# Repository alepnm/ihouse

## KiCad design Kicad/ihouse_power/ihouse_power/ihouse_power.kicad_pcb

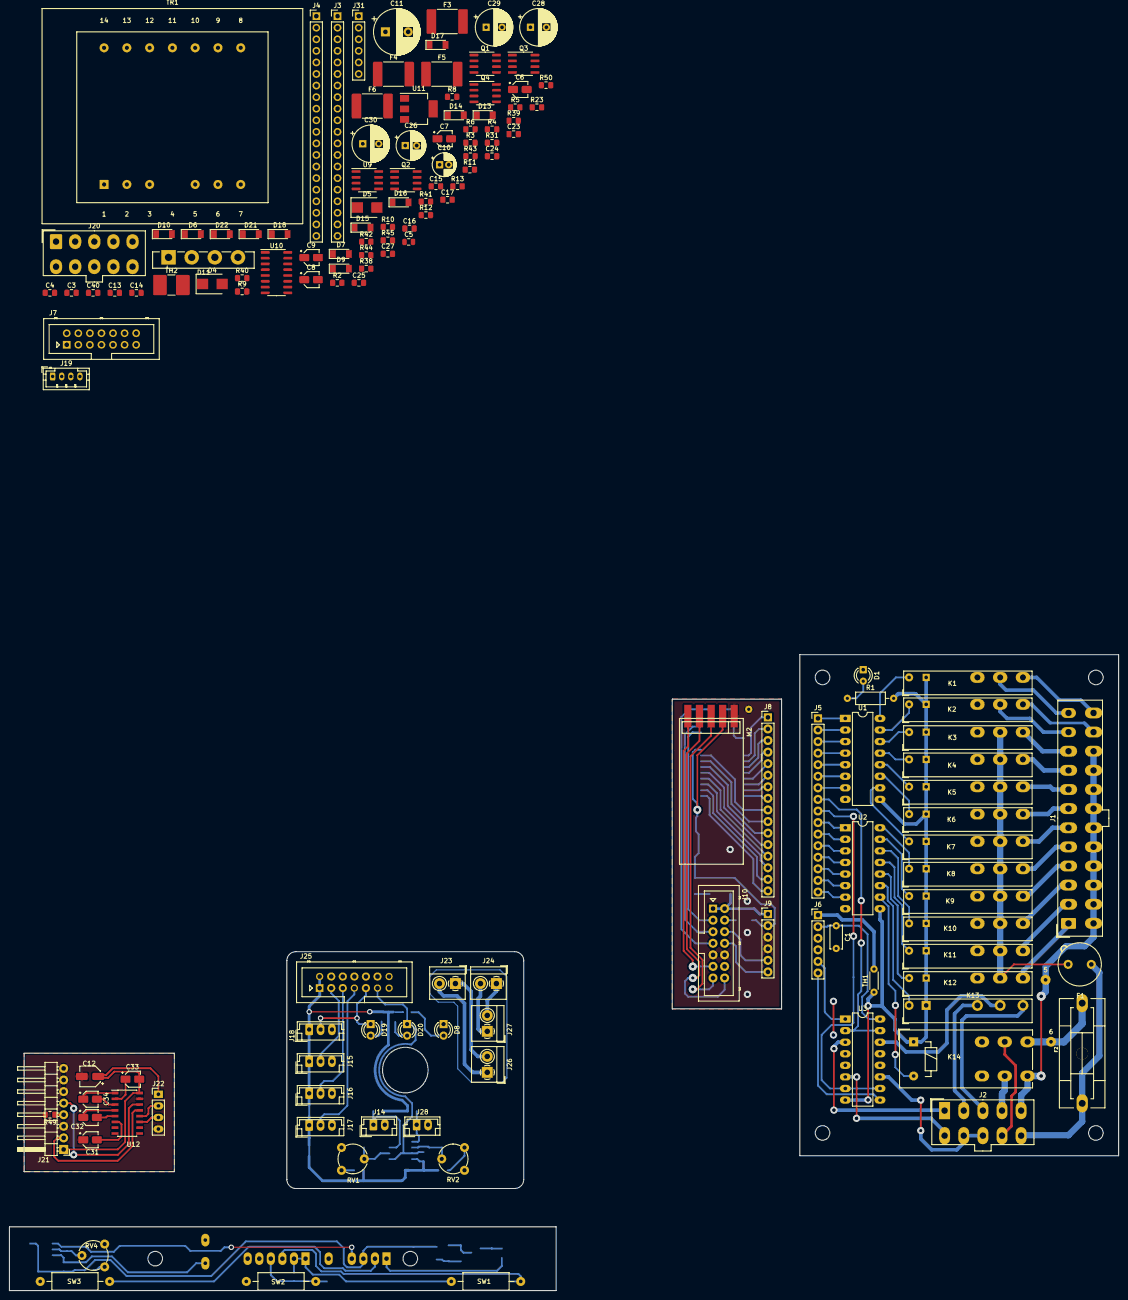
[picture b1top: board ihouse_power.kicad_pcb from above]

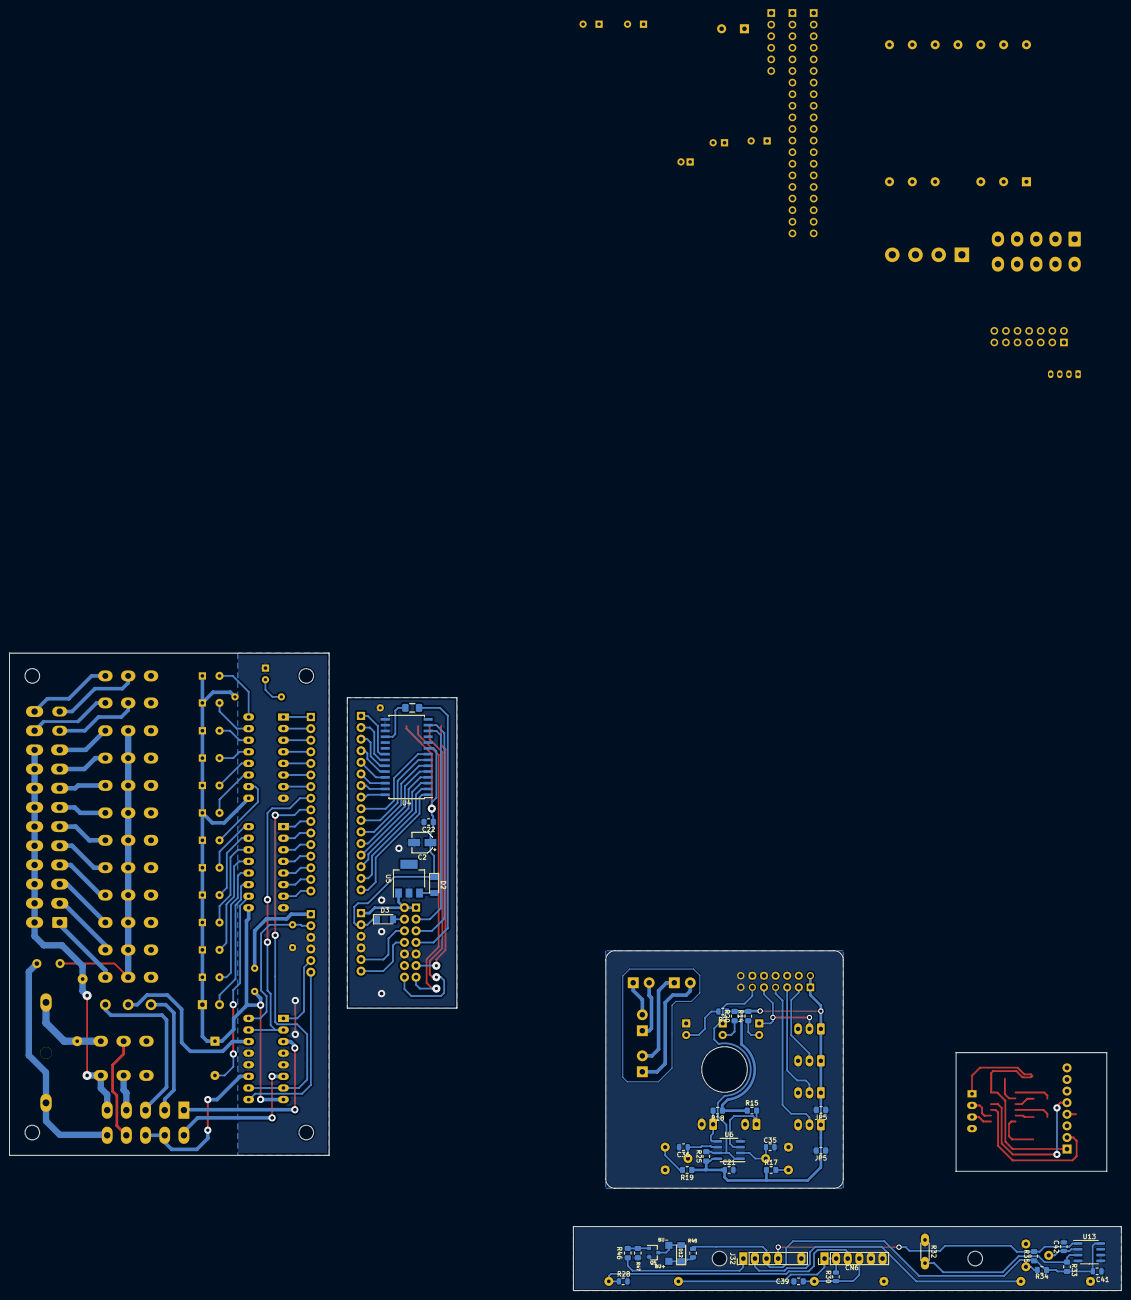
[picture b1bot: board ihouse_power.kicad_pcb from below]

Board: 2 copper layers, 243.5 x 139.6 mm, 178 parts (37 on the bottom side), 195 nets.

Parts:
5, 6: SolderWirePad_1x01_Drill0.8mm
C1: C; C_Disc_D5.0mm_W2.5mm_P5.00mm
C2: CP; CP_Elec_4x5.3
C3, C4, C13, C14, C15, C16, C17, C23, C24, C25, C40: 0.1; C_0805_2012Metric_Pad1.15x1.40mm_HandSolder
C5: 10n; C_0805_2012Metric
C6, C7, C8, C9, C31, C32, C33, C34: 10,0; CP_Elec_3x5.4
C10: CP; CP_Radial_D5.0mm_P2.00mm
C11: CP; CP_Radial_D10.0mm_P5.00mm
C12: 10,0; CP_Elec_4x4.5
C21, C35, C36, C41, C42: 0.1; C_0805_2012Metric
C22, C27, C39: C; C_0805_2012Metric_Pad1.15x1.40mm_HandSolder
C26: 100x16V; CP_Radial_D6.3mm_P2.50mm
C28, C29, C30: CP; CP_Radial_D8.0mm_P3.50mm
CN6: Conn_01x06; PinHeader_1x06_P2.54mm_Vertical
D1: LED; LED_D3.0mm
D2, D3, D6, D7, D10, D12, D13, D14, D15, D16, D17, D18, D22: BAS32; D_MiniMELF
D4, D5: FR2J; D_SMB
D8: POWER; LED_D3.0mm
D9, D21: BAS85; D_MiniMELF
D11: GBU6A; Diode_Bridge_Vishay_GBU
D19: DTH LINK; LED_D3.0mm
D20: PHOTO; LED_D3.0mm
F1: Fuse; Fuseholder_TR5_Littelfuse_No560_No460
F2: Fuse; Fuseholder5x20_horiz_SemiClosed_Casing10x25mm
F3, F4, F5, F6: 33V/3A; Fuse_2920_7451Metric_Pad2.10x5.45mm_HandSolder
J1: Conn_02x12_Top_Bottom; Molex_Mini-Fit_Jr_5566-24A_2x12_P4.20mm_Vertical
J2, J20: Conn_02x05_Top_Bottom; Molex_Mini-Fit_Jr_5566-10A_2x05_P4.20mm_Vertical
J3, J4: Conn_01x20; PinHeader_1x20_P2.54mm_Vertical
J5, J8: Conn_01x16; PinHeader_1x16_P2.54mm_Vertical
J6, J9, J31, J32: Conn_01x06; PinHeader_1x06_P2.54mm_Vertical
J7, J10: Conn_02x07_Odd_Even; Multicomp_MC9A12-1434_2x07_P2.54mm_Vertical
J14: OPT1; JST_EH_B2B-EH-A_1x02_P2.50mm_Vertical
J15: LEAK1; JST_EH_B3B-EH-A_1x03_P2.50mm_Vertical
J16: LEAK2; JST_EH_B3B-EH-A_1x03_P2.50mm_Vertical
J17: LEAK3; JST_EH_B3B-EH-A_1x03_P2.50mm_Vertical
J18: DHT22; JST_EH_B3B-EH-A_1x03_P2.50mm_Vertical
J19: I2C; JST_PH_B4B-PH-K_1x04_P2.00mm_Vertical
J21: RS232; PinHeader_1x08_P2.54mm_Horizontal
J22: Nextion; PinHeader_1x04_P2.54mm_Vertical
J23, J26: Valve1; TerminalBlock_4Ucon_1x02_P3.50mm_Horizontal
J24, J27: Valve2; TerminalBlock_4Ucon_1x02_P3.50mm_Horizontal
J25: Conn_01x14; Multicomp_MC9A12-1434_2x07_P2.54mm_Vertical
J28: OPT2; JST_EH_B2B-EH-A_1x02_P2.50mm_Vertical
JP5, JP5#2: 0R; R_0805_2012Metric_Pad1.15x1.40mm_HandSolder
K1, K2, K3, K4, K5, K6, K7, K8, K9, K10, K11, K12, K13: FINDER-34.51; Relay_SPDT_Finder_34.51_Vertical
K14: FINDER-41.52; Relay_DPDT_Finder_40.52
M2: tb387_uart_expander; TB387_UART_expander
Q1, Q2, Q3, Q4: IRF7403; SOIC-8_3.9x4.9mm_P1.27mm
Q5: BC847; SOT-23
R1: 4.7k; R_Axial_DIN0207_L6.3mm_D2.5mm_P10.16mm_Horizontal
R2: 47k; R_0805_2012Metric_Pad1.15x1.40mm_HandSolder
R3, R4, R5, R6, R12, R17, R19, R23, R34, R38, R39, R40, R41: 100; R_0805_2012Metric_Pad1.15x1.40mm_HandSolder
R7, R28, R30: 4.7k; R_0805_2012Metric
R8, R9, R14, R20: 4.7k; R_0805_2012Metric_Pad1.15x1.40mm_HandSolder
R10, R11, R15, R18, R33: R; R_0805_2012Metric_Pad1.15x1.40mm_HandSolder
R13, R25, R35, R42, R43, R44, R45, R46, R47, R49: 10k; R_0805_2012Metric_Pad1.15x1.40mm_HandSolder
R31: 47R; R_0805_2012Metric_Pad1.15x1.40mm_HandSolder
R32: R_PHOTO; R_Axial_DIN0204_L3.6mm_D1.6mm_P5.08mm_Horizontal
R48: 47; R_0805_2012Metric
R50: 1k; R_0805_2012Metric_Pad1.15x1.40mm_HandSolder
RV1, RV2, RV4: 5k; Potentiometer_Piher_PT-6-V_Vertical
SW1: BLDR; R_Axial_DIN0411_L9.9mm_D3.6mm_P15.24mm_Horizontal
SW2: USER; R_Axial_DIN0411_L9.9mm_D3.6mm_P15.24mm_Horizontal
SW3: RESET; R_Axial_DIN0411_L9.9mm_D3.6mm_P15.24mm_Horizontal
TH1: Thermistor_PTC; R_Axial_DIN0204_L3.6mm_D1.6mm_P5.08mm_Horizontal
TH2: Thermistor_PTC; R_2816_7142Metric
TR1: TEZ8.0 2x12V; Transformer_Breve_TEZ-47x57
U1, U2: ULN2004; DIP-16_W7.62mm_LongPads
U3: L293D; DIP-16_W7.62mm_LongPads
U4: MCP23017_SO; SOIC-28W_7.5x17.9mm_P1.27mm
U5: L7805; SOT-223
U6, U13: LM393; SOIC-8_3.9x4.9mm_P1.27mm
U9: 24LC32; SOIC-8_3.9x4.9mm_P1.27mm
U10, U12: MAX232; SOIC-16_3.9x9.9mm_P1.27mm
U11: L7805; SOT-223-3_TabPin2

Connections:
+12V: K1.A1, K2.A1, K3.A1, K4.A1, K5.A1, K6.A1, K7.A1, K8.A1, K9.A1, K10.A1, K11.A1, K12.A1, K13.A1, K14.A1, R1.2, TH1.1, U1.9, U2.9, U3.8
/5VDC: C12.1, C33.2, J21.1, J22.1, U12.16
/230L: F1.2, K3.11, K4.11, K5.11, K6.11, K7.11, K8.11, K9.11, K10.11, K11.11, K12.11
/230N: 5.1, J1.13, J1.14, J1.15, J1.16, J1.17, J1.18, J1.19, J1.20, J1.21, J1.22, J2.5, K14.24
/MCP23017 modulis/5VDC: D3.2, J10.4
/MCP23017 modulis/5VDC1: C2.1, C22.1, D2.1, D3.1, J9.2, M2.2, U4.9
/MCP23017 modulis/12VDC: J9.1, J10.1, J10.2, U5.1
/MCP23017 modulis/COM1: C2.2, C22.2, J9.3, J9.4, J10.9, J10.10, M2.1, U4.10, U4.15, U4.16, U4.17, U5.2
/MCP23017 modulis/GPA0: J8.1, U4.21
/MCP23017 modulis/GPA1: J8.2, U4.22
/MCP23017 modulis/GPA2: J8.3, U4.23
/MCP23017 modulis/GPA3: J8.4, U4.24
/MCP23017 modulis/GPA4: J8.5, U4.25
/MCP23017 modulis/GPA5: J8.6, U4.26
/MCP23017 modulis/GPA6: J8.7, U4.27
/MCP23017 modulis/GPB0: J8.16, U4.1
/MCP23017 modulis/GPB1: J8.15, U4.2
/MCP23017 modulis/GPB2: J8.14, U4.3
/MCP23017 modulis/GPB3: J8.13, U4.4
/MCP23017 modulis/GPB4: J8.12, U4.5
/MCP23017 modulis/GPB5: J8.11, U4.6
/MCP23017 modulis/GPB6: J8.10, U4.7
/MCP23017 modulis/M1EN: J9.5, J10.6
/MCP23017 modulis/M23EN: J9.6, J10.8
/MCP23017 modulis/MA: J8.8, U4.28
/MCP23017 modulis/MB: J8.9, U4.8
/MCP23017 modulis/SCL: J10.3, U4.12
/MCP23017 modulis/SDA: J10.5, U4.13
/MCP23017 modulis/TBRX: J10.14, M2.4
/MCP23017 modulis/TBTX: J10.13, M2.3
/MCP23017 modulis/~MCPRST: J10.7, U4.18
/MCP23017 modulis/~TBCMD: J10.11, M2.5
/MCU plokste/3V@1: CN6.1, R30.2, SW1.1
/MCU plokste/3VDC: D6.1, D7.1, D10.1, D13.1, D14.1, D15.1, D16.1, D17.1, D18.2, D22.1, J3.1, J4.18, R8.1, R9.1
/MCU plokste/5V@1: C41.1, J32.3, R33.1, R34.1, R35.1, R48.2, U13.8
/MCU plokste/5VDC: C8.2, C24.1, C25.1, C26.1, C40.1, J3.3, J7.4, J19.1, J31.3, R31.1, U9.8, U10.16, U11.3
/MCU plokste/5VDDA: C13.1, R31.2
/MCU plokste/12VDC: C11.1, C23.1, D4.1, D5.1, D9.2, J4.20, J7.1, J7.2, U11.1
/MCU plokste/BUZMN: D12.2, Q5.3
/MCU plokste/BUZPL: D12.1, R48.1
/MCU plokste/COM: C3.2, C4.2, C5.2, C6.1, C10.2, C11.2, C13.2, C14.2, C15.2, C16.2, C17.2, C23.2, C24.2, C25.2, C26.2, C27.2, C28.2, C29.2, C30.2, C40.2, D11.4, J3.2, J4.19, J7.9, J7.10, J19.4, J31.5, J31.6, Q1.1, Q1.2, Q1.3, Q2.1, Q2.2, Q2.3, Q3.1, Q3.2, Q3.3, Q4.1, Q4.2, Q4.3, R11.2, R13.1, R42.1, R43.1, R44.1, R45.1, TH2.1, U9.1, U9.2, U9.3, U9.4, U9.7, U10.15, U11.2
/MCU plokste/COM@1: C39.2, C41.2, C42.2, CN6.5, CN6.6, J32.5, J32.6, Q5.2, R28.1, R32.1, R47.1, RV4.1, SW2.1, SW3.1, U13.4, U13.5, U13.6
/MCU plokste/LPULSE: D4.2, R2.1, TR1.8
/MCU plokste/M1ENA: J3.19, J7.6
/MCU plokste/M23ENA: J3.18, J7.8
/MCU plokste/OPTIC: J31.4, R23.2
/MCU plokste/PA0: C27.1, D10.2, J4.5, R10.2, R11.1
/MCU plokste/PA1: C4.1, D13.2, J4.6, R4.1
/MCU plokste/PA2: J4.7, U10.11
/MCU plokste/PA3: J4.8, U10.12
/MCU plokste/PA4: C15.1, D14.2, J4.9, R5.1
/MCU plokste/PA5: C16.1, D15.2, J4.10, R6.1
/MCU plokste/PA6: C14.1, D6.2, J4.11, R23.1
/MCU plokste/PA7: C3.1, D7.2, J4.12, R3.1
/MCU plokste/PA8: D22.2, J3.16, R50.1
/MCU plokste/PA11: J3.13, J31.1
/MCU plokste/PB3: C5.1, D17.2, J3.10, R2.2, R13.2
/MCU plokste/PC13: D16.2, J4.2, R12.1
/MCU plokste/PWM1: J3.9, R38.2
/MCU plokste/PWM2: J3.8, R39.2
/MCU plokste/PWM3: J4.13, R40.2
/MCU plokste/PWM4: J4.14, R41.2
/MCU plokste/SCL: J3.7, J7.3, J19.2, R9.2, U9.6
/MCU plokste/SDA: J3.6, J7.5, J19.3, R8.2, U9.5
/MCU plokste/TBRX: J3.15, J7.14
/MCU plokste/TBTX: J3.14, J7.13
/MCU plokste/VB: C28.1, C29.1, C30.1, D11.1, J20.7, J20.8, J20.9, J20.10
/MCU plokste/VBAT: C17.1, D18.1, D21.1
/MCU plokste/~MCPRST: J3.20, J7.7
/MCU plokste/~TBCMD: J3.17, J7.11
/NEXRX: J22.2, U12.12
/NEXTX: J22.3, U12.11
/Paskirstymo dezute/5VDC: C21.1, J15.1, J16.1, J17.1, J18.1, J25.1, J25.2, R7.1, R14.2, R15.1, R17.1, R18.1, R19.1, R20.2, R25.1, U6.8
/Paskirstymo dezute/COM: C21.2, C35.2, C36.2, D8.1, J25.10, J25.12, J25.13, J25.14, JP5.1, JP5.2, JP5#2.1, JP5#2.2, RV1.3, RV2.3, U6.4
/Paskirstymo dezute/DHTIO: D19.1, J18.2, J25.9
/Paskirstymo dezute/LEAK1: J15.2, J25.3
/Paskirstymo dezute/LEAK2: J16.2, J25.5
/Paskirstymo dezute/LEAK3: J17.2, J25.7
/Paskirstymo dezute/OPT1: J14.1, R15.2, U6.3
/Paskirstymo dezute/OPT2: J28.1, R18.2, U6.5
/Paskirstymo dezute/OPTICWC: D20.1, J25.11, R25.2, U6.1, U6.7
/Paskirstymo dezute/V1A: J23.1, J26.2
/Paskirstymo dezute/V1B: J23.2, J26.1
/Paskirstymo dezute/V2A: J24.1, J27.2
/Paskirstymo dezute/V2B: J24.2, J27.1
/RSRX: J21.2, U12.13
/RSTX: J21.5, U12.14
/Reliu modulis/5VDC: C1.1, J6.2, U3.16
/Reliu modulis/12VDC: J6.1, TH1.2
/Reliu modulis/COM1: C1.2, D1.1, J6.3, J6.4, U1.8, U2.8, U3.4, U3.5, U3.12, U3.13
/Reliu modulis/K1: K1.A2, U1.16
/Reliu modulis/K1.11: J1.12, K1.11
/Reliu modulis/K1.14: J1.24, K1.14
/Reliu modulis/K2: K2.A2, U1.15
/Reliu modulis/K2.11: J1.11, K2.11
/Reliu modulis/K2.14: J1.23, K2.14
/Reliu modulis/K3: K3.A2, U1.14
/Reliu modulis/K3L: J1.10, K3.14
/Reliu modulis/K4: K4.A2, U1.13
/Reliu modulis/K4L: J1.9, K4.14
/Reliu modulis/K5: K5.A2, U1.12
/Reliu modulis/K5L: J1.8, K5.14
/Reliu modulis/K6: K6.A2, U1.11
/Reliu modulis/K6L: J1.7, K6.14
/Reliu modulis/K7: K7.A2, U1.10
/Reliu modulis/K7L: J1.6, K7.14
/Reliu modulis/K8: K8.A2, U2.16
/Reliu modulis/K8L: J1.5, K8.14
/Reliu modulis/K9: K9.A2, U2.15
/Reliu modulis/K9L: J1.4, K9.14
/Reliu modulis/K10: K10.A2, U2.14
/Reliu modulis/K10L: J1.3, K10.14
/Reliu modulis/K11: K11.A2, U2.13
/Reliu modulis/K11L: J1.2, K11.14
/Reliu modulis/K12: K12.A2, U2.12
/Reliu modulis/K12L: J1.1, K12.14
/Reliu modulis/K13: K13.A2, U2.11
/Reliu modulis/K14: K14.A2, U2.10
/Reliu modulis/K14L: J2.9, K14.11
/Reliu modulis/K14N: J2.4, K14.21
/Reliu modulis/M1A: J2.1, U3.3
/Reliu modulis/M1B: J2.6, U3.6
/Reliu modulis/M1ENA: J6.5, U3.1
/Reliu modulis/M2A: J2.2, K13.12
/Reliu modulis/M2B: J2.7, J2.8, U3.11
/Reliu modulis/M3A: J2.3, K13.14
/Reliu modulis/M23ENA: J6.6, U3.9
/Reliu modulis/MA: J5.8, U3.2, U3.15
/Reliu modulis/MB: J5.9, U3.7, U3.10
/Reliu modulis/REL1: J5.1, U1.1
/Reliu modulis/REL2: J5.2, U1.2
/Reliu modulis/REL3: J5.3, U1.3
/Reliu modulis/REL4: J5.4, U1.4
/Reliu modulis/REL5: J5.5, U1.5
/Reliu modulis/REL6: J5.6, U1.6
/Reliu modulis/REL7: J5.7, U1.7
/Reliu modulis/REL8: J5.10, U2.1
/Reliu modulis/REL9: J5.11, U2.2
/Reliu modulis/REL10: J5.12, U2.3
/Reliu modulis/REL11: J5.13, U2.4
/Reliu modulis/REL12: J5.14, U2.5
/Reliu modulis/REL13: J5.15, U2.6
/Reliu modulis/REL14: J5.16, U2.7
/Reliu modulis/VACL: F1.1, F2.1, J2.10
unnamed: C6.2, U10.6
unnamed: C7.1, U10.4
unnamed: C7.2, U10.5
unnamed: C8.1, U10.2
unnamed: C9.1, U10.1
unnamed: C9.2, U10.3
unnamed: C10.1, D9.1, R10.1
unnamed: C12.2, C31.1, J21.3, J21.6, J21.7, J21.8, J22.4, R49.2, U12.15
unnamed: C31.2, U12.6
unnamed: C32.1, U12.4
unnamed: C32.2, U12.5
unnamed: C33.1, U12.2
unnamed: C34.1, U12.1
unnamed: C34.2, U12.3
unnamed: C35.1, RV1.2, U6.2
unnamed: C36.1, RV2.2, U6.6
unnamed: C39.1, CN6.4, R30.1, SW2.2
unnamed: C42.1, RV4.2, U13.2
unnamed: CN6.3, R28.2, SW1.2
unnamed: D1.2, R1.1
unnamed: D2.2, U5.3
unnamed: D5.2, TR1.14
unnamed: D8.2, R7.2
unnamed: D11.2, J20.6
unnamed: D11.3, J20.1
unnamed: D19.2, R14.1
unnamed: D20.2, R20.1
unnamed: 6.1, F2.2, K14.14
unnamed: F3.1, J20.2
unnamed: F3.2, Q1.5, Q1.6, Q1.7, Q1.8
unnamed: F4.1, J20.3
unnamed: F4.2, Q2.5, Q2.6, Q2.7, Q2.8
unnamed: F5.1, J20.4
unnamed: F5.2, Q3.5, Q3.6, Q3.7, Q3.8
unnamed: F6.1, J20.5
unnamed: F6.2, Q4.5, Q4.6, Q4.7, Q4.8
unnamed: J21.4, R49.1
unnamed: J32.1, R46.2
unnamed: J32.2, SW3.2
unnamed: J32.4, R35.2, U13.1
unnamed: K13.11, U3.14
unnamed: Q1.4, R38.1, R42.2
unnamed: Q2.4, R39.1, R43.2
unnamed: Q3.4, R40.1, R44.2
unnamed: Q4.4, R41.1, R45.2
unnamed: Q5.1, R46.1, R47.2
unnamed: R17.2, RV1.1
unnamed: R19.2, RV2.1
unnamed: R32.2, R33.2, U13.3
unnamed: R34.2, RV4.3
unnamed: TH2.2, TR1.9, TR1.13

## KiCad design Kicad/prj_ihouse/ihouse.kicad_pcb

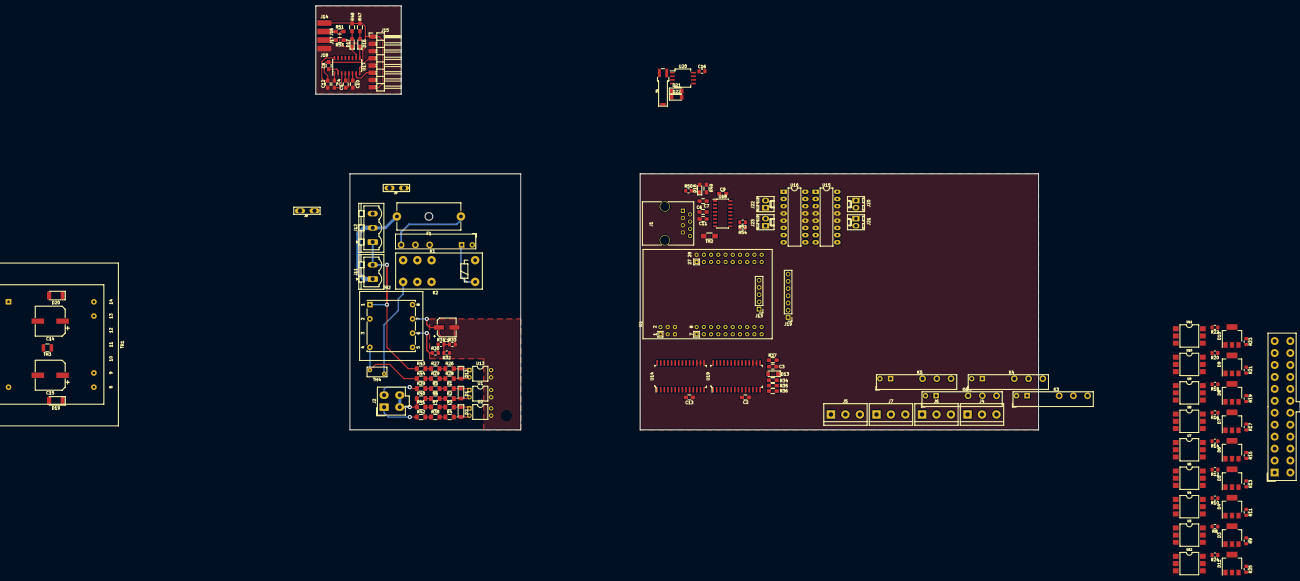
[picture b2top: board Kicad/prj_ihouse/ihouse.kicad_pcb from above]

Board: 2 copper layers, 254.0 x 149.0 mm, 143 parts (0 on the bottom side), 129 nets.

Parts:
C1: 100uFx16V; CP_Elec_6.3x5.7
C2, C3, C13: 0.1; C_0805_HandSoldering
C4, C5, C6, C7, C8, C9, C10, C11, C12: 1u; C_0805_HandSoldering
C14, C15: CP; CP_Elec_10x7.9
C16: 15p; C_0805_2012Metric_Pad1.15x1.40mm_HandSolder
D1, D2, D12: LL4148; D_MiniMELF
D3, D4, D5, D6, D7, D8, D9, D10, D11: Z0103MN; SOT-223
D13: BAS32; D_MiniMELF
D16: RX; LED_0805_HandSoldering
D17: TX; LED_0805_HandSoldering
D18: RC; LED_0805_HandSoldering
D19, D20: LL4004; D_MELF
D21, D22: BAS85; D_MiniMELF
F1: 5A; Fuseholder_Cylinder-5x20mm_Schurter_0031_8201_Horizontal_Op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
J1: UART2; RJ45_8
J2: AC Inputs; Molex_Mini-Fit_Jr_5566-04A_2x02_P4.20mm_Vertical
J3: AC OUTS; Molex_MiniFit-JR-5556-24A_2x12x4.20mm_Straight
J4: EXT1; TerminalBlock_bornier-3_P5.08mm
J5: EXT2; TerminalBlock_bornier-3_P5.08mm
J6: EXT3; TerminalBlock_bornier-3_P5.08mm
J7: EXT4; TerminalBlock_bornier-3_P5.08mm
J8, J9: Conn_01x01; Faston_6.3x0.8x14
J11: To AC/DC; PhoenixContact_MSTBVA_2,5_2-G_1x02_P5.00mm_Vertical
J12: Conn_01x03; PhoenixContact_MSTBVA_2,5_3-G_1x03_P5.00mm_Vertical
J13: UART1; Pin_Header_Straight_1x05_Pitch2.54mm
J14, J16, J17, J18: Conn_01x01; SolderWirePad_single_SMD_5x10mm
J15: Conn_01x08; Pin_Header_Angled_1x08_Pitch2.54mm
J19: EV1527; Pin_Header_Straight_1x07_Pitch2.54mm
J20: Valve1; Molex_KK-6410-02_02x2.54mm_Straight
J21: Valve2; Molex_KK-6410-02_02x2.54mm_Straight
J22: Valve3; Molex_KK-6410-02_02x2.54mm_Straight
J23: Valve4; Molex_KK-6410-02_02x2.54mm_Straight
K1, K3, K4, K5, K6: FINDER-34.51; Relay_SPDT_Finder_34.51_Vertical
K2: RT42xxxx; Relay_DPDT_Finder_40.52
M1: unicon_v1
R1, R2, R3, R4, R5, R6, R7, R26, R27, R28, R29, R38, R39, R40, R41, R42, R43, R44: 33k; R_1206_3216Metric_Pad1.42x1.75mm_HandSolder
R8, R9, R10, R11, R12, R13, R14, R15, R16, R17, R18, R19, R20, R21, R22, R23, R24, R25: R; R_0805_2012Metric_Pad1.15x1.40mm_HandSolder
R30, R50, R52, R54: 1k; R_0805_2012Metric_Pad1.15x1.40mm_HandSolder
R31: 120; R_0805_2012Metric_Pad1.15x1.40mm_HandSolder
R32, R33: Rx; R_0805_2012Metric_Pad1.15x1.40mm_HandSolder
R34: 15k; R_0805_HandSoldering
R35, R36, R37, R47, R48, R51, R53: 1k; R_0805_HandSoldering
R49: 2k; R_0805_HandSoldering
TH2: 1210L005WR; R_1206_HandSoldering
TH3: 1.5A/30V; R_1210_3225Metric
TH4: 0.5A/230V; RV_Disc_D7mm_W3.4mm_P5mm
TR1: TSZZ20-006M_1; Transformer_Breve_TEZ-47x57_1
TR2: Transformer_TEZ_22x24_6V; Transformer_Breve_TEZ-22x24
U1, U2, U13: LTV-817; DIP-4_W7.62mm
U3, U4, U5, U7, U8, U9, U10, U11, U12: MOC3060S; DIP-6_W9.53mm_SMD
U14, U19: MCP23017; SOIC-28_W7.5mm
U15, U16: L293D; DIP-16_W7.62mm_LongPads
U17: St232C; SOIC-16_3.9x9.9mm_Pitch1.27mm
U18: ST232C; SOIC-16_3.9x9.9mm_Pitch1.27mm
U20: PCF8583; SO-8_5.3x6.2mm_P1.27mm
Y1: Crystal; Crystal_32768_horizontal

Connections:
/3VDC: D22.2, M1.3, R32.1
/5VDC: C2.1, C9.1, C13.1, D13.1, J13.5, J19.2, M1.2, R34.1, R35.2, R36.2, R37.1, R49.1, TH2.1, U14.9, U15.16, U16.16, U18.16, U19.9
/12VDC: C14.1, C15.1, D19.1, D20.1, K1.A1, K2.A1, K3.A1, K4.A1, K5.A1, K6.A1, M1.1, U15.8, U16.8
/ACL: D3.2, D3.4, D4.2, D4.4, D5.2, D5.4, D6.2, D6.4, D7.2, D7.4, D8.2, D8.4, D9.2, D9.4, D10.2, D10.4, D11.2, D11.4, K1.11, R8.1, R10.1, R12.1, R14.1, R16.1, R18.1, R20.1, R22.1, R24.1
/ACN: J3.16, J3.17, J3.18, J3.19, J3.20, J3.21, J3.22, J3.23, J3.24, J11.2, J12.1, K2.24, R43.1, TR1.1, TR2.1
/COM: C1.2, C2.2, C3.2, C11.1, C13.2, C14.2, C15.2, J1.3, J1.5, J1.7, J13.4, J19.1, M1.4, M1.5, M1.6, M1.28, R33.2, TH3.1, U1.3, U2.3, U13.3, U14.10, U14.15, U14.16, U14.17, U15.4, U15.5, U15.12, U15.13, U16.4, U16.5, U16.12, U16.13, U18.15, U19.10, U19.16, U19.17, U20.3, U20.4
/DIRA: U15.2, U15.10, U16.2, U16.10
/DIRB: U15.7, U15.15, U16.7, U16.15
/EXT1_11: J4.2, K3.11
/EXT1_12: J4.3, K3.12
/EXT1_14: J4.1, K3.14
/EXT2_11: J5.2, K5.11
/EXT2_12: J5.3, K5.12
/EXT2_14: J5.1, K5.14
/EXT3_11: J6.2, K4.11
/EXT3_12: J6.3, K4.12
/EXT3_14: J6.1, K4.14
/EXT4_11: J7.2, K6.11
/EXT4_12: J7.3, K6.12
/EXT4_14: J7.1, K6.14
/LPULSE: M1.45, U13.4
/OUTAC1: D3.1, J3.1, R9.2, U3.4
/OUTAC2: D4.1, J3.2, R11.2, U4.4
/OUTAC3: D5.1, J3.3, R13.2, U5.4
/OUTAC4: D6.1, J3.4, R15.2, U7.4
/OUTAC5: D7.1, J3.5, R17.2, U8.4
/OUTAC6: D8.1, J3.6, R19.2, U9.4
/OUTAC7: D9.1, J3.7, R21.2, U10.4
/OUTAC8: D10.1, J3.8, R23.2, U11.4
/OUTAC9: D11.1, J3.9, R25.2, U12.4
/PE: J8.1, J9.1, J12.3
/RS232 interfeisas/NEX_5VDC: C8.2, C12.2, J14.1, J15.1, J15.8, R47.1, R48.1, U17.16
/RS232 interfeisas/NEX_COM: C10.2, C12.1, J15.2, J15.3, J15.5, J15.7, J18.1, U17.15
/RS232 interfeisas/NEX_RX: J17.1, R53.2
/RS232 interfeisas/NEX_TX: J16.1, R51.2
/RS232 interfeisas/RS5VDC: J1.1, J1.8, TH2.2
/RS232 interfeisas/RSCNTRL: D18.1, J1.2, R50.2
/RS232 interfeisas/RSRX: J1.6, U18.8
/RS232 interfeisas/RSTX: J1.4, U18.7
/RS232 interfeisas/RXN: J15.4, U17.8
/RS232 interfeisas/TXN: J15.6, U17.7
/SCL: M1.10, R35.1, U14.12, U19.12, U20.6
/SDA: M1.11, R36.1, U14.13, U19.13, U20.5
/UART2_RX: M1.22, R54.1
/UART2_TX: M1.21, R52.1
/UART_DE: J13.1, M1.38
/UART_RX: J13.2, M1.40
/UART_TX: J13.3, M1.39
/VLINE: M1.19, R30.2, R31.1
/~MCPRST: C3.1, D13.2, R34.2, U14.18, U19.18
unnamed: C1.1, R31.2, R32.2, R33.1, TR2.7
unnamed: C4.1, U17.1
unnamed: C4.2, U17.3
unnamed: C5.1, U17.4
unnamed: C5.2, U17.5
unnamed: C6.1, U18.4
unnamed: C6.2, U18.5
unnamed: C7.1, U18.1
unnamed: C7.2, U18.3
unnamed: C8.1, U17.2
unnamed: C9.2, U18.2
unnamed: C10.1, U17.6
unnamed: C11.2, U18.6
unnamed: C16.1, D21.1, D22.1, U20.8
unnamed: C16.2, U20.1, Y1.2
unnamed: D1.1, R1.2, U1.1
unnamed: D1.2, R2.2, U1.2
unnamed: D2.1, R3.2, U2.1
unnamed: D2.2, R4.2, U2.2
unnamed: D3.3, R9.1
unnamed: D4.3, R11.1
unnamed: D5.3, R13.1
unnamed: D6.3, R15.1
unnamed: D7.3, R17.1
unnamed: D8.3, R19.1
unnamed: D9.3, R21.1
unnamed: D10.3, R23.1
unnamed: D11.3, R25.1
unnamed: D12.1, R26.2, U13.1
unnamed: D12.2, R28.2, U13.2
unnamed: D16.1, R53.1, U17.9
unnamed: D16.2, R47.2
unnamed: D17.1, R51.1, U17.10
unnamed: D17.2, R48.2
unnamed: D18.2, R49.2
unnamed: D19.2, TR1.8
unnamed: D20.2, TR1.14
unnamed: F1.1, K1.14
unnamed: F1.2, J11.1, J12.2, K2.14, TH4.2
unnamed: J2.1, R42.1
unnamed: J2.2, R39.1
unnamed: J2.3, J2.4, R40.1, R41.1
unnamed: J20.1, U15.3
unnamed: J20.2, U15.6
unnamed: J21.1, U15.11
unnamed: J21.2, U15.14
unnamed: J22.1, U16.3
unnamed: J22.2, U16.6
unnamed: J23.1, U16.11
unnamed: J23.2, U16.14
unnamed: R1.1, R5.2
unnamed: R2.1, R6.2
unnamed: R3.1, R7.2
unnamed: R8.2, U3.6
unnamed: R10.2, U4.6
unnamed: R12.2, U5.6
unnamed: R14.2, U7.6
unnamed: R16.2, U8.6
unnamed: R18.2, U9.6
unnamed: R20.2, U10.6
unnamed: R22.2, U11.6
unnamed: R24.2, U12.6
unnamed: R26.1, R27.2
unnamed: R27.1, R43.2
unnamed: R28.1, R29.2
unnamed: R29.1, R44.2
unnamed: R30.1, TR2.6
unnamed: R37.2, U19.15
unnamed: R38.1, R42.2
unnamed: R4.1, R38.2
unnamed: R5.1, R39.2
unnamed: R6.1, R40.2
unnamed: R7.1, R41.2
unnamed: R44.1, TH4.1, TR1.7, TR2.4
unnamed: R52.2, U18.10
unnamed: R54.2, U18.9
unnamed: TH3.2, TR1.9, TR1.13
unnamed: U3.1, U4.1, U5.1, U7.1, U8.1, U9.1, U10.1, U11.1, U12.1
unnamed: U20.2, Y1.1

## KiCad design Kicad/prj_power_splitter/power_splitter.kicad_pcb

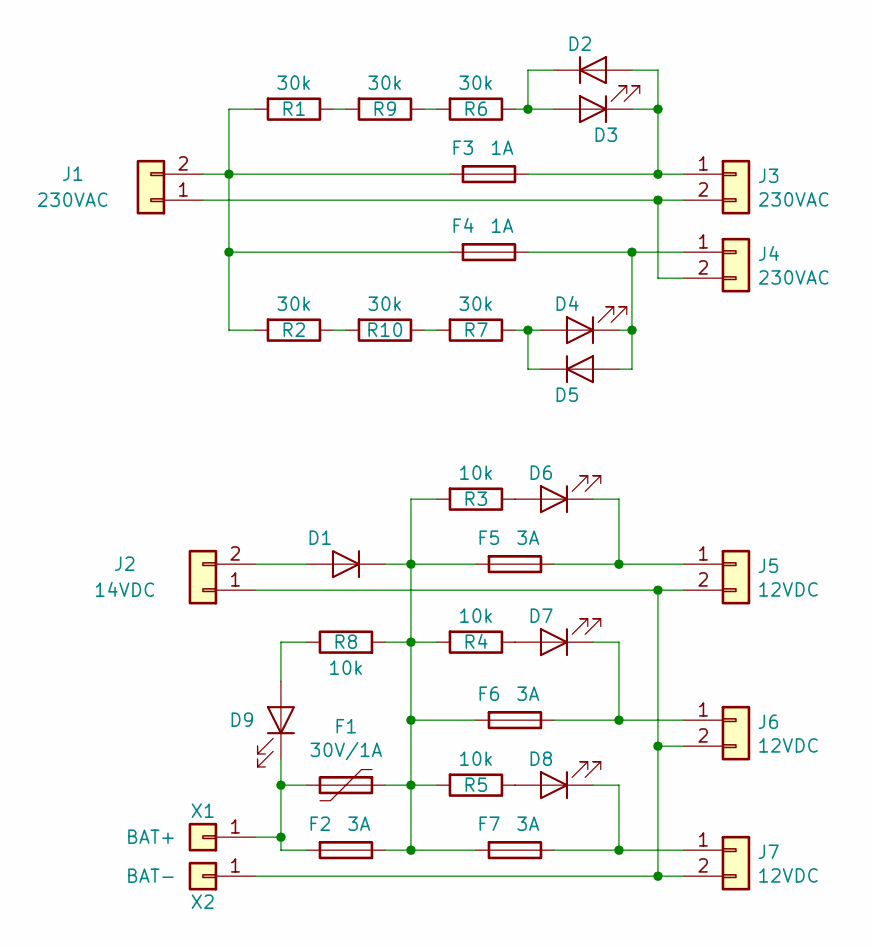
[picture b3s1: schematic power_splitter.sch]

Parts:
D1: D; D_5KPW_P12.70mm_Horizontal
D2, D5: 1N4148; D_MiniMELF
D3, D4, D6, D7, D8, D9: LED; LED_D3.0mm
F1: 30V/1A; R_2816_7142Metric
F2, F5, F6, F7: 3A; Fuseholder_Cylinder-5x20mm_Schurter_0031_8201_Horizontal_Op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
F3, F4: 1A; Fuseholder_Cylinder-5x20mm_Schurter_0031_8201_Horizontal_Op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
J1, J3, J4: 230VAC; TerminalBlock_Phoenix_MKDS-1,5-2_1x02_P5.00mm_Horizontal
J2: 14VDC; PhoenixContact_MSTBVA_2,5_2-G_1x02_P5.00mm_Vertical
J5, J6, J7: 12VDC; PhoenixContact_MSTBVA_2,5_2-G_1x02_P5.00mm_Vertical
R1, R2, R6, R7, R9, R10: 30k; R_1206_3216Metric
R3, R4, R5, R8: 10k; R_1206_3216Metric
X1: BAT+; Faston_6.3x0.8x14
X2: BAT-; Faston_6.3x0.8x14

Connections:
unnamed: D1.1 (K), F1.1, F2.1, F5.2, F6.2, F7.2, R3.2, R4.2, R5.2, R8.2
unnamed: D1.2 (A), J2.2
unnamed: D2.1 (K), D3.2 (A), R6.1
unnamed: D2.2 (A), D3.1 (K), F3.1, J3.1
unnamed: D4.1 (K), D5.2 (A), F4.1, J4.1
unnamed: D4.2 (A), D5.1 (K), R7.1
unnamed: D6.1 (K), F5.1, J5.1
unnamed: D6.2 (A), R3.1
unnamed: D7.1 (K), F6.1, J6.1
unnamed: D7.2 (A), R4.1
unnamed: D8.1 (K), F7.1, J7.1
unnamed: D8.2 (A), R5.1
unnamed: D9.1 (K), F1.2, F2.2, X1.1
unnamed: D9.2 (A), R8.1
unnamed: F3.2, F4.2, J1.2, R1.2, R2.2
unnamed: J1.1, J3.2, J4.2
unnamed: J2.1, J5.2, J6.2, J7.2, X2.1
unnamed: R1.1, R9.2
unnamed: R6.2, R9.1
unnamed: R7.2, R10.1
unnamed: R2.1, R10.2

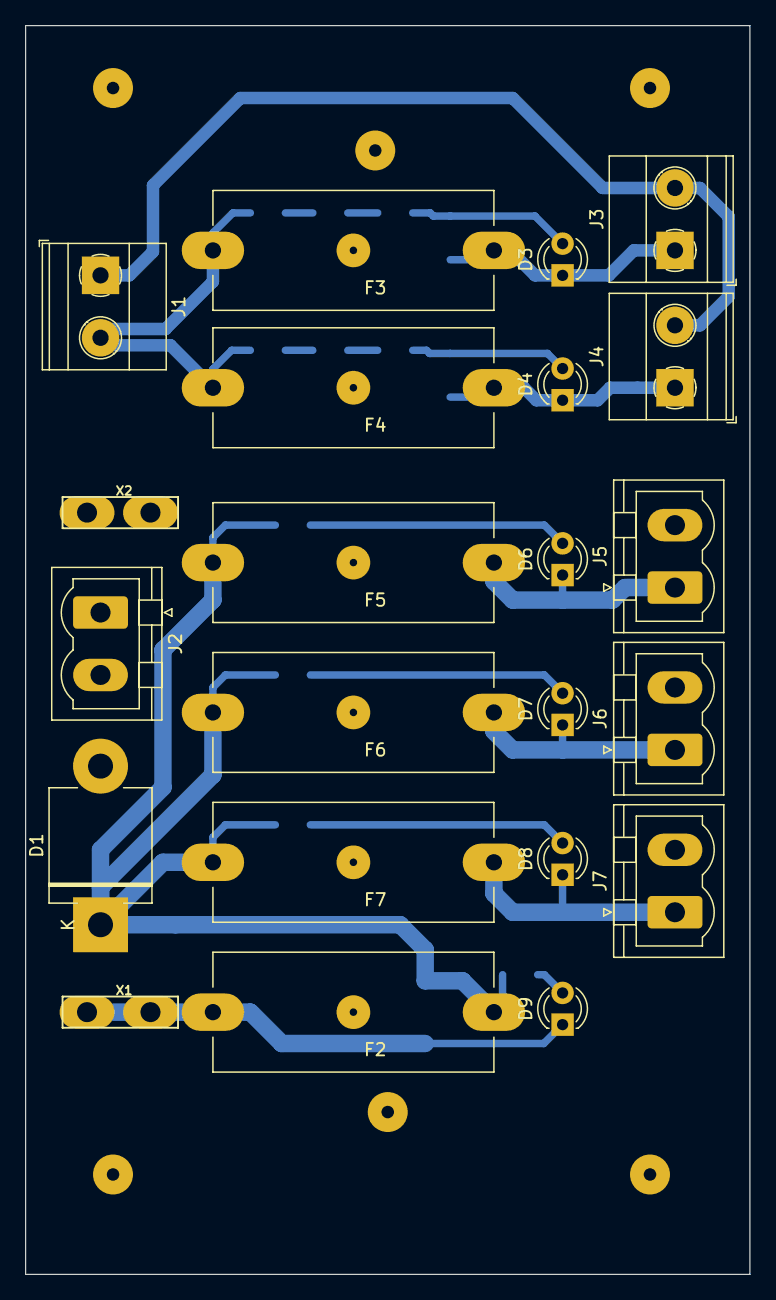
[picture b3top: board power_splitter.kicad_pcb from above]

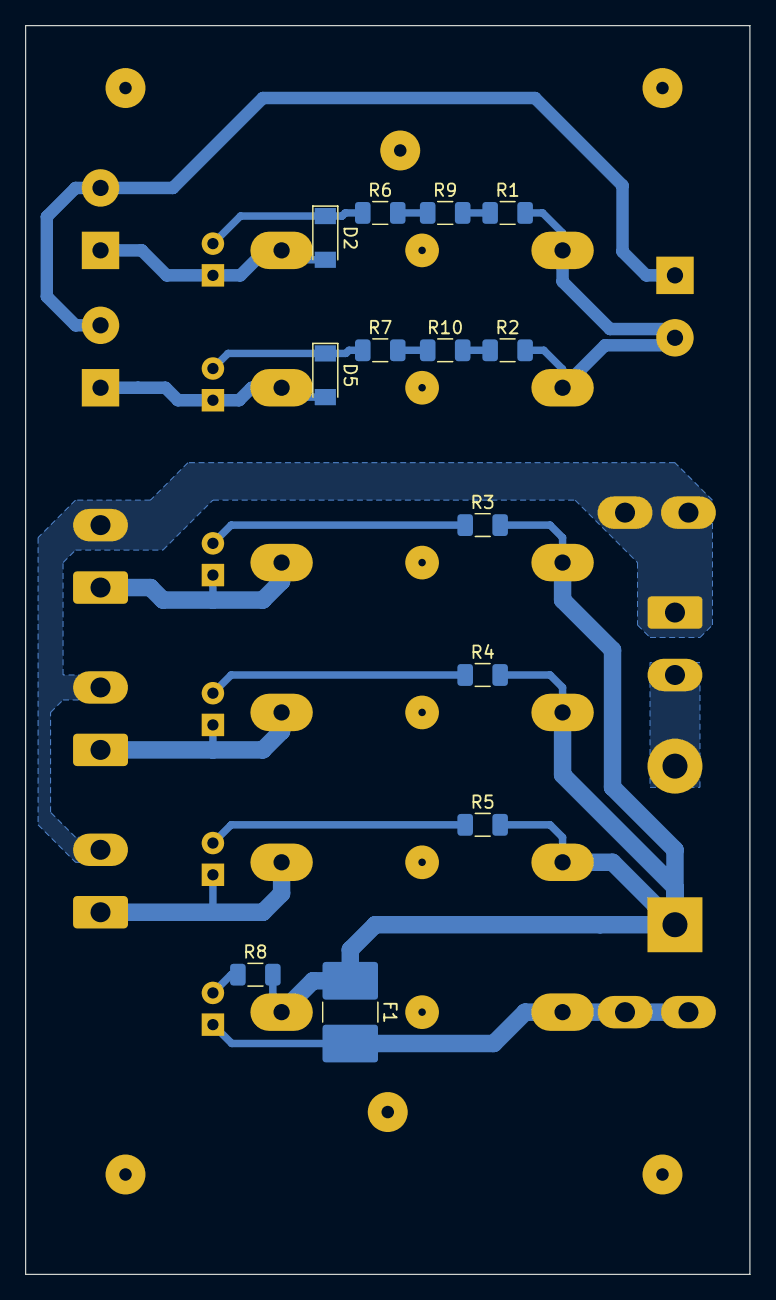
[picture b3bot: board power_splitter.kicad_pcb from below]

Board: 2 copper layers, 58.0 x 100.0 mm, 35 parts (13 on the bottom side), 21 nets.

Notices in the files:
Software/Controller/Core/Src/main.c:
COPYRIGHT(c) 2019 STMicroelectronics
(C) COPYRIGHT STMicroelectronics *****END OF FILE
